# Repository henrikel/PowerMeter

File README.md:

# PowerMeter
A power meter to monitor your electrical consumption using a phototransistor that counts pulses from a photodiode in the energy meter.

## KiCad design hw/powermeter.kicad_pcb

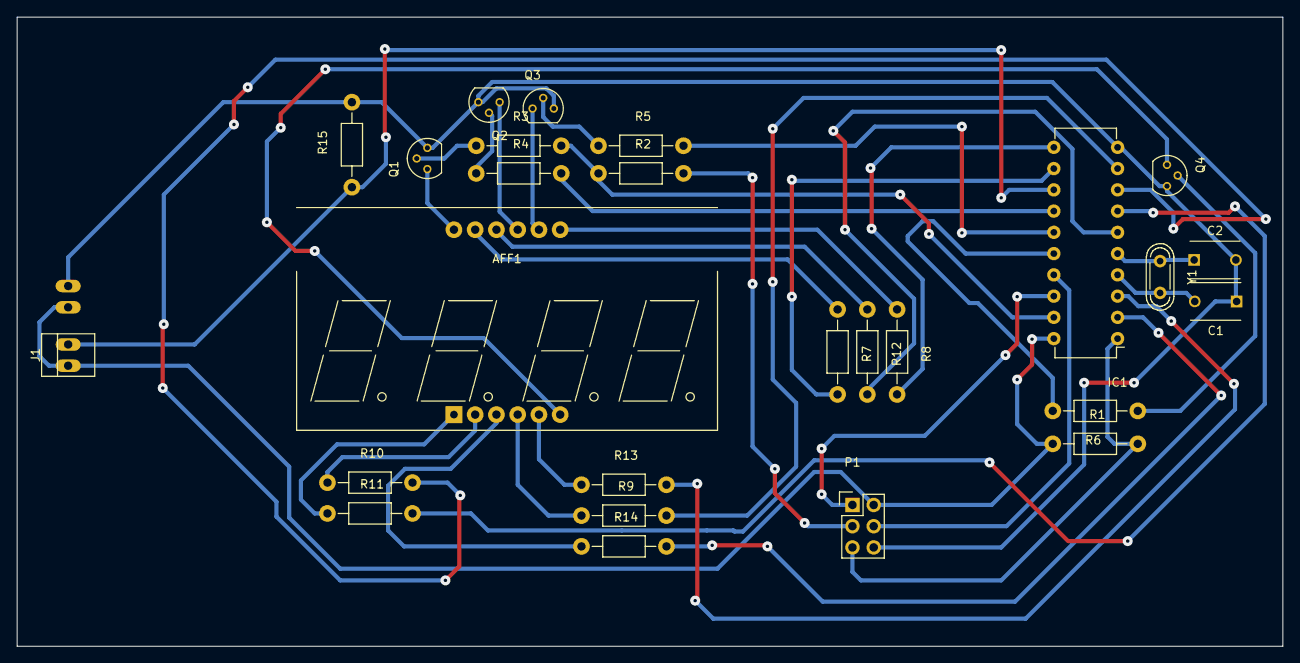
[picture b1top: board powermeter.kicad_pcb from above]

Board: 2 copper layers, 151.3 x 75.2 mm, 27 parts (1 on the bottom side), 37 nets.

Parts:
AFF1: CC56-12; Big-Cx56-12
C1, C2: 22p; C_Disc_D6_P5
IC1: ATTINY2313-P; DIP-20_W7.62mm
J1, J2: Screw_Terminal_1x02; PINHEAD1-2
P1: CONN_02X03; Pin_Header_Straight_2x03
Q1, Q2, Q3, Q4: BC237; TO-92_Molded_Narrow
R1, R2: 4k7; Resistor_Horizontal_RM10mm
R3, R4, R5, R6: 22k; Resistor_Horizontal_RM10mm
R7, R8, R9, R10, R11, R12, R13, R14: 180; Resistor_Horizontal_RM10mm
R15: 1k; Resistor_Horizontal_RM10mm
Y1: 8 MHz; Crystal_HC52-U_Vertical

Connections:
GND: C1.1, C2.2, IC1.10, J2.2, P1.6, Q1.3, Q2.3, Q3.3, Q4.3, R15.2
unnamed: AFF1.1, R11.1
unnamed: AFF1.2, R10.1
unnamed: AFF1.3, R14.1
unnamed: AFF1.4, R9.1
unnamed: AFF1.5, R13.1
unnamed: AFF1.6, Q4.1
unnamed: AFF1.7, R8.1
unnamed: AFF1.8, Q3.1
unnamed: AFF1.9, Q2.1
unnamed: AFF1.10, R12.1
unnamed: AFF1.11, R7.1
unnamed: AFF1.12, Q1.1
unnamed: C1.2, IC1.4, Y1.2
unnamed: C2.1, IC1.5, Y1.1
unnamed: IC1.1, P1.5, R1.2
unnamed: IC1.2, R14.2
unnamed: IC1.3, R13.2
unnamed: IC1.6, R12.2
unnamed: IC1.7, R11.2
unnamed: IC1.8, R10.2
unnamed: IC1.9, R9.2
unnamed: IC1.11, R8.2
unnamed: IC1.12, R7.2
unnamed: IC1.13, J1.2, R15.1
unnamed: IC1.14, R4.2
unnamed: IC1.15, R5.2
unnamed: IC1.16, R6.2
unnamed: IC1.17, P1.4
unnamed: IC1.18, P1.1
unnamed: IC1.19, R2.1, R3.2
unnamed: P1.3, R2.2
unnamed: Q1.2, R3.1
unnamed: Q2.2, R4.1
unnamed: Q3.2, R5.1
unnamed: Q4.2, R6.1
VCC: IC1.20, J1.1, J2.1, P1.2, R1.1

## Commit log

2022-07-25 Add code
2022-07-25 New license
2022-08-01 Added schematic images
